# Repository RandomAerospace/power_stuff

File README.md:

if you want to add more stuff, use library loader and set path of downloaded footprints to SAMACSYS_LIB_PDB on my repo!
additionally, please set path preferences based on relative path of the folder that you have pulled the github repo into.
Go to UREX PDB  folder under POWER DISTRIBUTION for the pimped up weather balloon PDB

Power board presentation:https://drive.google.com/file/d/1bSlgJGe3XdCi3mun8Qso9A9fgnM_BNgd/view?usp=sharing

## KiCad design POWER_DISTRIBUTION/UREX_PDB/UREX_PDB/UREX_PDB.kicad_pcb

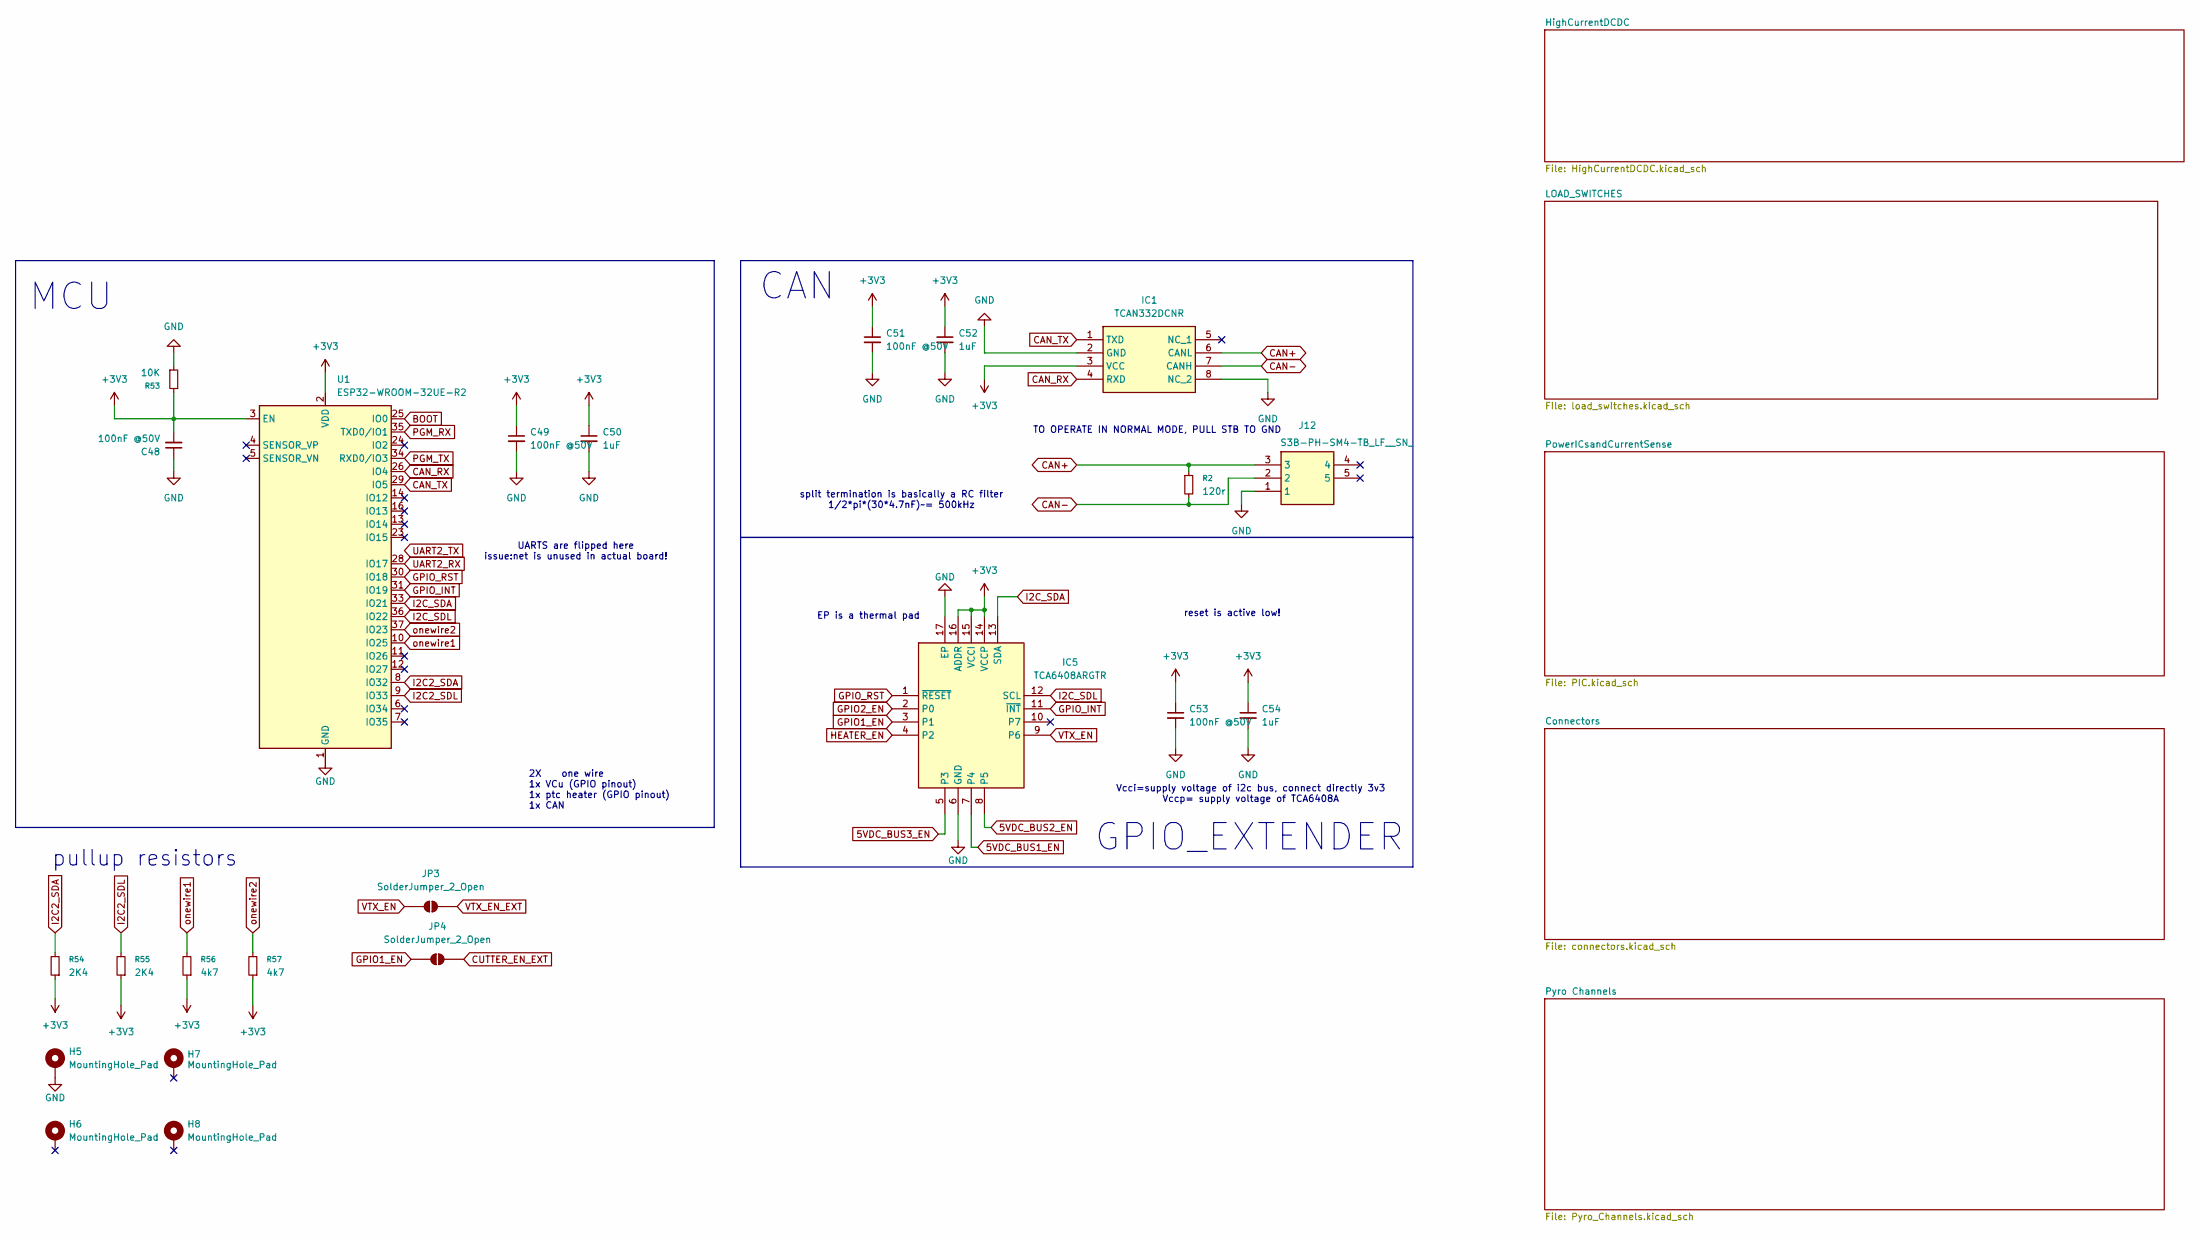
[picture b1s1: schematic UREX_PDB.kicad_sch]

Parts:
C48, C49, C51, C53: 100nF @50V; C_0603_1608Metric
C50, C52, C54: 1uF; C_0603_1608Metric
H5, H7, H8: MountingHole_Pad; MountingHole_2.2mm_M2_ISO7380
H6: MountingHole_Pad; MountingHole_2.2mm_M2_Pad_Via
IC1: TCAN332DCNR; SOT65P280X145-8N; Mouser Part Number 595-TCAN332DCNR
IC5: TCA6408ARGTR; QFN50P300X300X100-17N-D; Mouser Part Number 595-TCA6408ARGTR
J12: S3B-PH-SM4-TB_LF__SN_; S3BPHSM4TBLFSN; Mouser Part Number N/A
JP3, JP4: SolderJumper_2_Open; SolderJumper-2_P1.3mm_Open_Pad1.0x1.5mm
R2: 120r; R_0603_1608Metric
R53: 10K; R_0603_1608Metric
R54, R55: 2K4; R_0603_1608Metric
R56, R57: 4k7; R_0603_1608Metric
U1: ESP32-WROOM-32UE-R2; ESP32-WROOM-32UE

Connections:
5VDC_BUS1_EN: IC5.7 (P4); also elsewhere on the board
5VDC_BUS2_EN: IC5.8 (P5); also elsewhere on the board
5VDC_BUS3_EN: IC5.5 (P3); also elsewhere on the board
+3V3: C48.2, C49.1, C50.1, C51.1, C52.1, C53.1, C54.1, IC1.3 (VCC), IC5.14 (VCCP), IC5.15 (VCCI), IC5.16 (ADDR), R53.2, R54.1, R55.1, R56.1, R57.1, U1.2 (VDD), U1.3 (EN); also elsewhere on the board
BOOT: U1.25 (IO0); also elsewhere on the board
CAN+: IC1.6 (CANL), J12.3, R2.1
CAN-: IC1.7 (CANH), J12.2, R2.2
CAN_RX: IC1.4 (RXD), U1.26 (IO4)
CAN_TX: IC1.1 (TXD), U1.29 (IO5)
CUTTER_EN_EXT: JP4.2 (B); also elsewhere on the board
GND: C48.1, C49.2, C50.2, C51.2, C52.2, C53.2, C54.2, H5.1, IC1.2 (GND), IC1.8 (NC_2), IC5.6 (GND), IC5.17 (EP), J12.1, R53.1, U1.1 (GND), U1.15 (GND), U1.38 (GND), U1.39 (GND); also elsewhere on the board
GPIO1_EN: IC5.3 (P1), JP4.1 (A); also elsewhere on the board
GPIO2_EN: IC5.2 (P0); also elsewhere on the board
GPIO_INT: IC5.11 (~INT), U1.31 (IO19)
GPIO_RST: IC5.1 (~RESET), U1.30 (IO18)
HEATER_EN: IC5.4 (P2); also elsewhere on the board
I2C2_SDA: R54.2, U1.8 (IO32); also elsewhere on the board
I2C2_SDL: R55.2, U1.9 (IO33); also elsewhere on the board
I2C_SDA: IC5.13 (SDA), U1.33 (IO21)
I2C_SDL: IC5.12 (SCL), U1.36 (IO22)
PGM_RX: U1.35 (TXD0/IO1); also elsewhere on the board
PGM_TX: U1.34 (RXD0/IO3); also elsewhere on the board
UART2_RX: U1.28 (IO17)
VTX_EN: IC5.9 (P6), JP3.1 (A); also elsewhere on the board
VTX_EN_EXT: JP3.2 (B); also elsewhere on the board
onewire1: R56.2, U1.10 (IO25); also elsewhere on the board
onewire2: R57.2, U1.37 (IO23); also elsewhere on the board

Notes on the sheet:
UARTS are flipped here issue:net is unused in actual board!
TO OPERATE IN NORMAL MODE, PULL STB TO GND
reset is active low!
pullup resistors
Vcci=supply voltage of i2c bus, connect directly 3v3 Vccp= supply voltage of TCA6408A
MCU
EP is a thermal pad
2X one wire 1x VCu (GPIO pinout) 1x ptc heater (GPIO pinout) 1x CAN
GPIO_EXTENDER
split termination is basically a RC filter 1/2*pi*(30*4.7nF)~= 500kHz
CAN

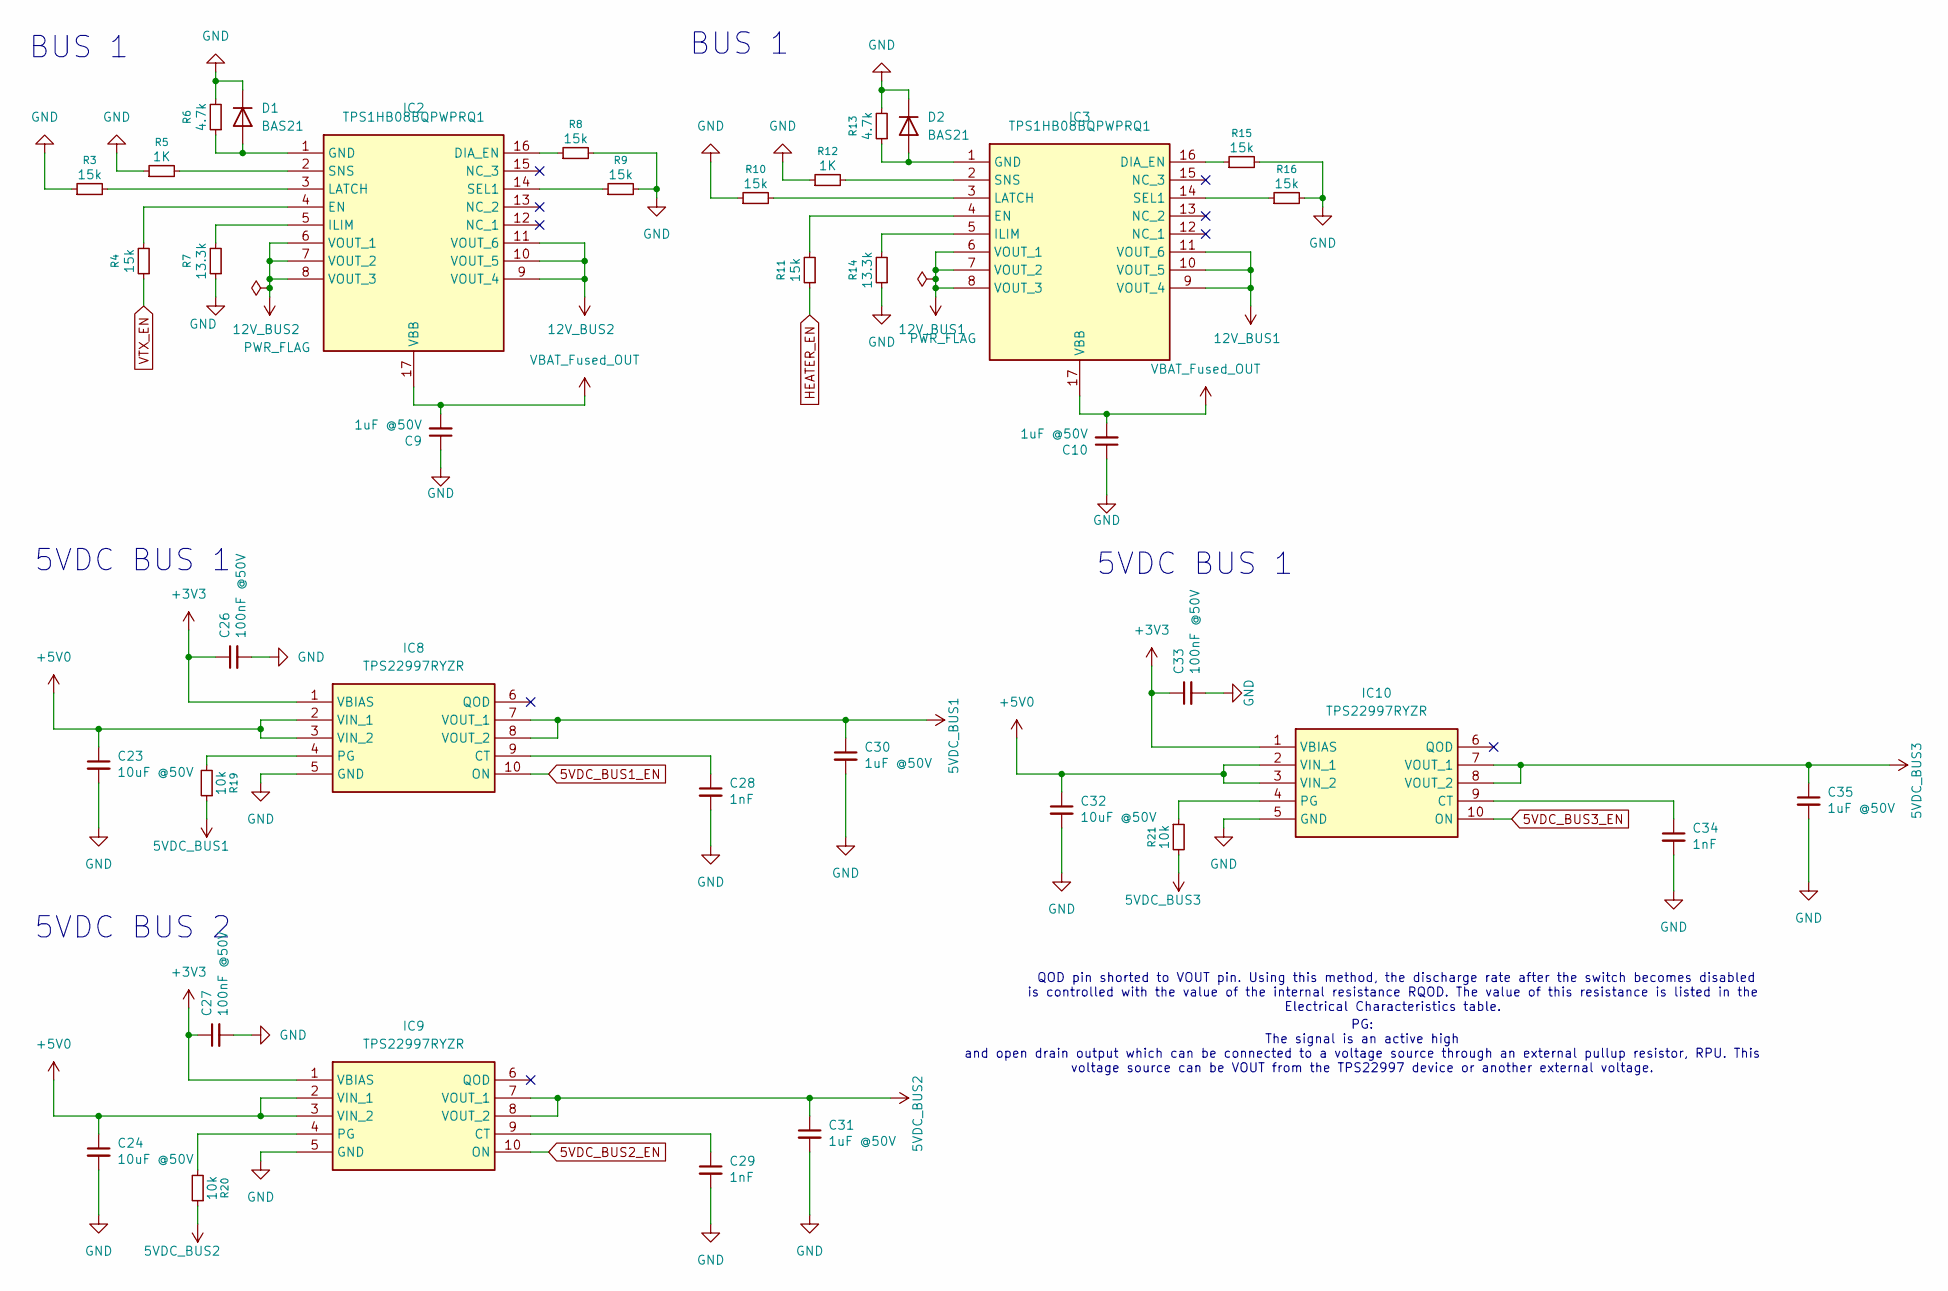
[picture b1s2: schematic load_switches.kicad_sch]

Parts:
C9, C10: 1uF @50V; C_0805_2012Metric_Pad1.18x1.45mm_HandSolder
C23, C24: 10uF @50V; C_1210_3225Metric_Pad1.33x2.70mm_HandSolder; Manufacturer_Part_Number GRM32EC72A106KE05L
C26, C27, C33: 100nF @50V; C_0402_1005Metric_Pad0.74x0.62mm_HandSolder
C28, C29, C34: 1nF; C_0603_1608Metric
C30, C31, C35: 1uF @50V; C_0805_2012Metric
C32: 10uF @50V; C_1210_3225Metric; Manufacturer_Part_Number GRM32EC72A106KE05L
D1, D2: BAS21; SOT-23
IC2, IC3: TPS1HB08BQPWPRQ1; SOP65P640X120-17N; Mouser Part Number 595-TPS1HB08BQPWPRQ1
IC8, IC9, IC10: TPS22997RYZR; Mouser Part Number 595-TPS22997RYZR
R3, R4, R8, R9, R10, R11, R15, R16: 15k; R_0603_1608Metric
R5, R12: 1K; R_0603_1608Metric
R6, R13: 4.7k; R_0603_1608Metric
R7, R14: 13.3k; R_0603_1608Metric
R19, R20, R21: 10k; R_0402_1005Metric_Pad0.72x0.64mm_HandSolder

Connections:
5VDC_BUS1: C30.1, IC8.7 (VOUT_1), IC8.8 (VOUT_2), R19.1; also elsewhere on the board
5VDC_BUS1_EN: IC8.10 (ON); also elsewhere on the board
5VDC_BUS2: C31.1, IC9.7 (VOUT_1), IC9.8 (VOUT_2), R20.1; also elsewhere on the board
5VDC_BUS2_EN: IC9.10 (ON); also elsewhere on the board
5VDC_BUS3: C35.1, IC10.7 (VOUT_1), IC10.8 (VOUT_2), R21.2; also elsewhere on the board
5VDC_BUS3_EN: IC10.10 (ON); also elsewhere on the board
12V_BUS1: IC3.6 (VOUT_1), IC3.7 (VOUT_2), IC3.8 (VOUT_3), IC3.9 (VOUT_4), IC3.10 (VOUT_5), IC3.11 (VOUT_6); also elsewhere on the board
12V_BUS2: IC2.6 (VOUT_1), IC2.7 (VOUT_2), IC2.8 (VOUT_3), IC2.9 (VOUT_4), IC2.10 (VOUT_5), IC2.11 (VOUT_6); also elsewhere on the board
+3V3: C26.1, C27.1, C33.1, IC8.1 (VBIAS), IC9.1 (VBIAS), IC10.1 (VBIAS); also elsewhere on the board
+5V0: C23.1, C24.1, C32.1, IC8.2 (VIN_1), IC8.3 (VIN_2), IC9.2 (VIN_1), IC9.3 (VIN_2), IC10.2 (VIN_1), IC10.3 (VIN_2); also elsewhere on the board
GND: C9.1, C10.1, C23.2, C24.2, C26.2, C27.2, C28.2, C29.2, C30.2, C31.2, C32.2, C33.2, C34.2, C35.2, D1.3 (K), D2.3 (K), IC8.5 (GND), IC9.5 (GND), IC10.5 (GND), R3.1, R5.1, R6.2, R7.1, R8.2, R9.2, R10.1, R12.1, R13.2, R14.1, R15.2, R16.2; also elsewhere on the board
HEATER_EN: R11.1; also elsewhere on the board
unnamed: D1.1 (A), IC2.1 (GND), R6.1
unnamed: D2.1 (A), IC3.1 (GND), R13.1
unnamed: IC2.16 (DIA_EN), R8.1
unnamed: IC2.4 (EN), R4.2
unnamed: IC2.5 (ILIM), R7.2
unnamed: IC2.3 (LATCH), R3.2
unnamed: IC2.14 (SEL1), R9.1
unnamed: IC2.2 (SNS), R5.2
unnamed: IC3.16 (DIA_EN), R15.1
unnamed: IC3.4 (EN), R11.2
unnamed: IC3.5 (ILIM), R14.2
unnamed: IC3.3 (LATCH), R10.2
unnamed: IC3.14 (SEL1), R16.1
unnamed: IC3.2 (SNS), R12.2
unnamed: C28.1, IC8.9 (CT)
unnamed: IC8.4 (PG), R19.2
unnamed: C29.1, IC9.9 (CT)
unnamed: IC9.4 (PG), R20.2
unnamed: C34.1, IC10.9 (CT)
unnamed: IC10.4 (PG), R21.1
VBAT_Fused_OUT: C9.2, C10.2, IC2.17 (VBB), IC3.17 (VBB); also elsewhere on the board
VTX_EN: R4.1; also elsewhere on the board

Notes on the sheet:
5VDC BUS 2
BUS 1
5VDC BUS 1
PG: The signal is an active high and open drain output which can be connected to a voltage source through an external pullup resistor, RPU. This voltage source can be VOUT from the TPS22997 device or another external voltage.
QOD pin shorted to VOUT pin. Using this method, the discharge rate after the switch becomes disabled is controlled with the value of the internal resistance RQOD. The value of this resistance is listed in the Electrical Characteristics table.

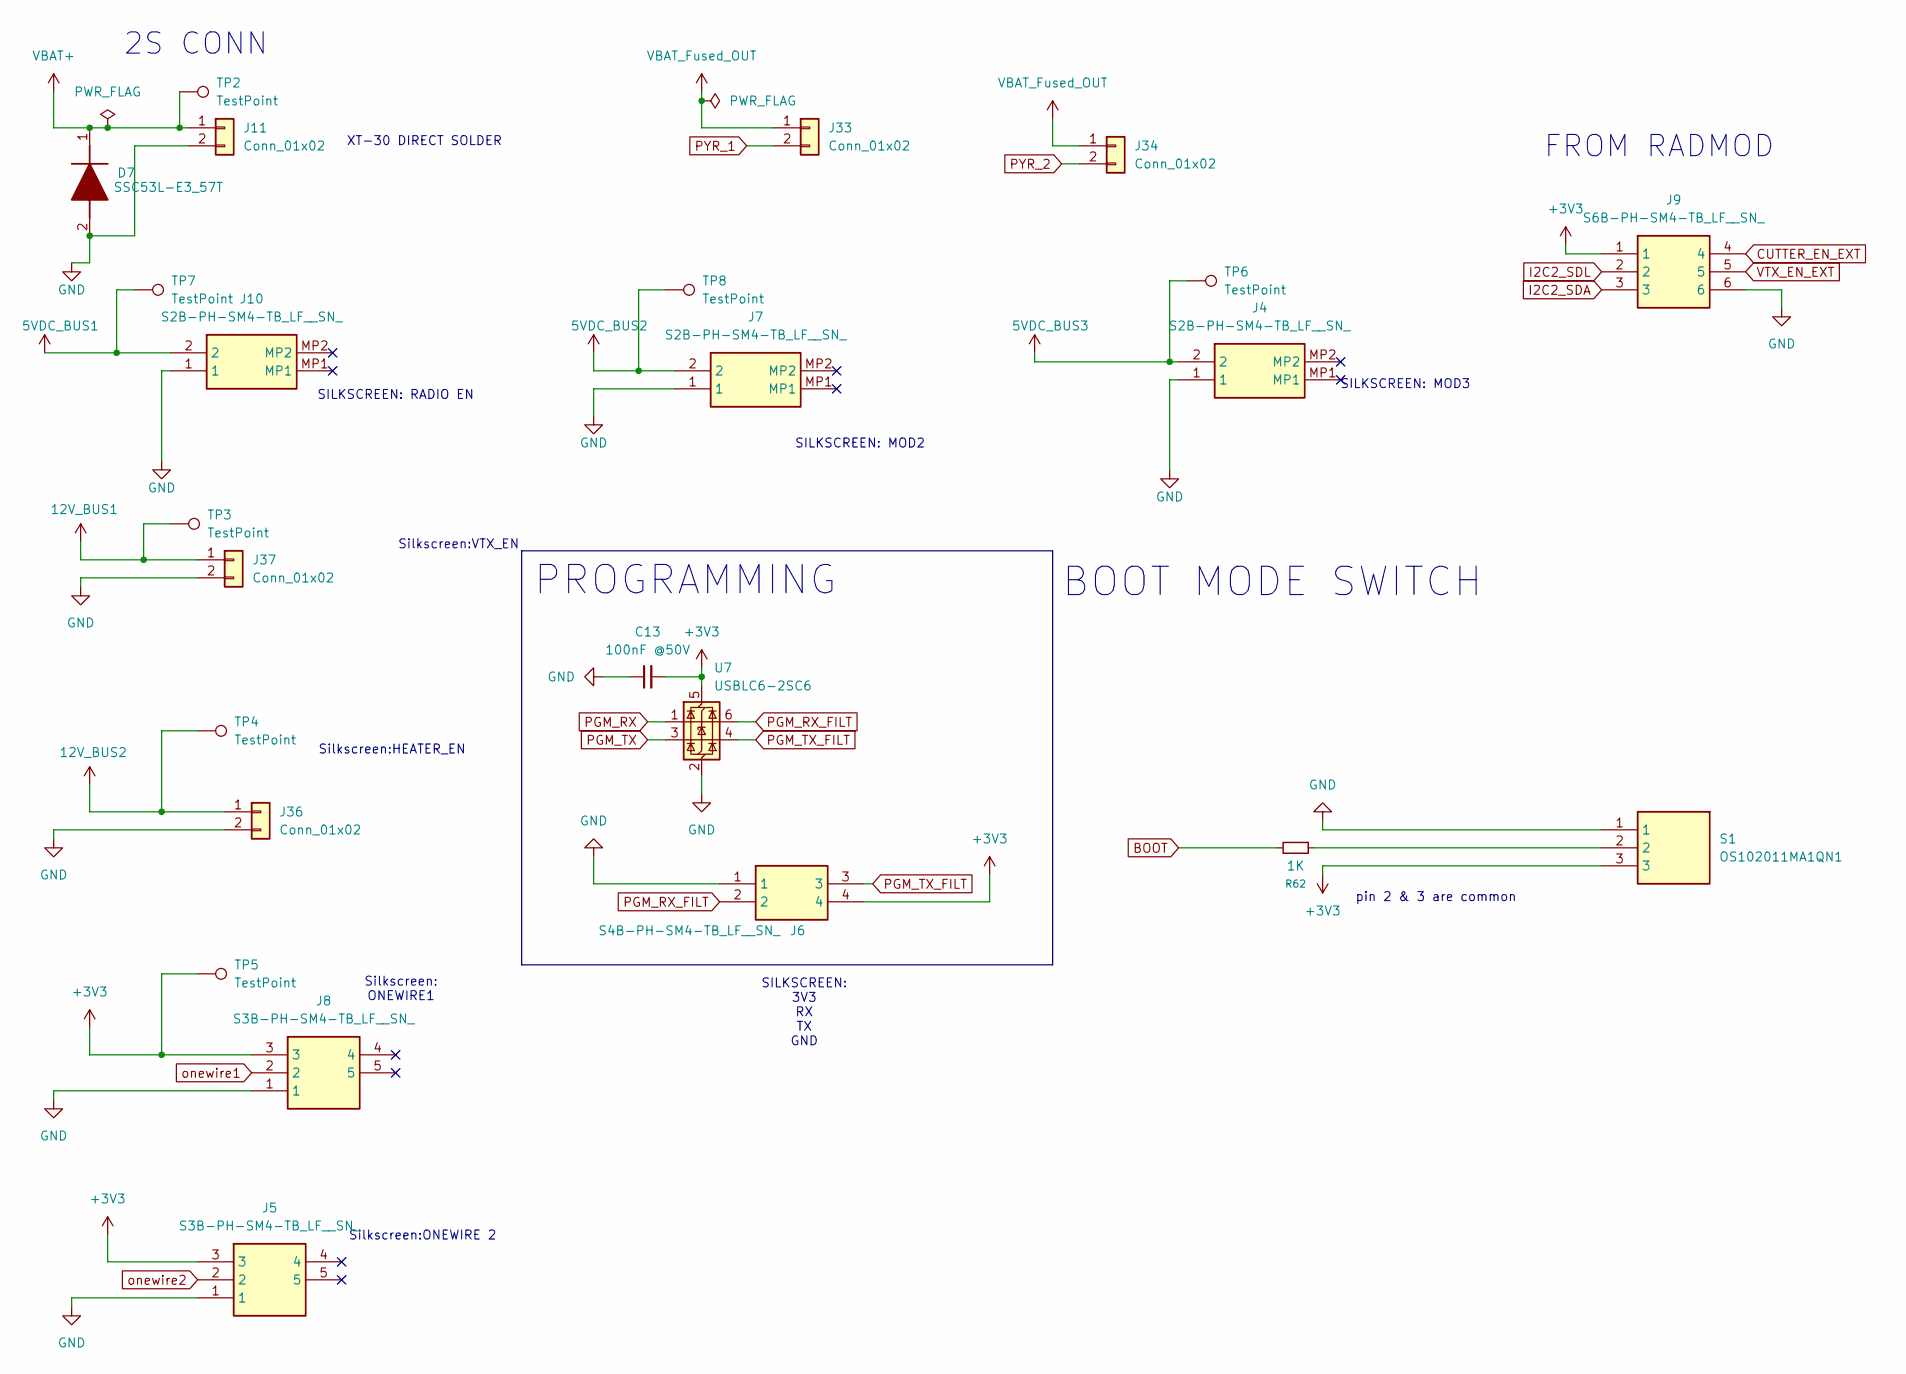
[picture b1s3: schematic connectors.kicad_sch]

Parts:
C13: 100nF @50V; C_0603_1608Metric
D7: SSC53L-E3_57T; DIOM7959X262N; Manufacturer_Part_Number SSC53L-E3/57T; Mouser Part Number 625-SSC53L-E3
J4, J7, J10: S2B-PH-SM4-TB_LF__SN_; S2BPHSM4TBLFSN; Mouser Part Number N/A
J5, J8: S3B-PH-SM4-TB_LF__SN_; S3BPHSM4TBLFSN; Mouser Part Number N/A
J6: S4B-PH-SM4-TB_LF__SN_; S4B-PH-SM4-TB; Mouser Part Number N/A
J9: S6B-PH-SM4-TB_LF__SN_; S6B-PH-SM4-TB_LF__SN__3; Mouser Part Number N/A
J11: Conn_01x02; AMASS_XT30U-F_1x02_P5.0mm_Vertical
J33, J34, J36, J37: Conn_01x02; JST_PH_S2B-PH-K_1x02_P2.00mm_Horizontal
R62: 1K; R_0603_1608Metric
S1: OS102011MA1QN1; SW_Slide_SPDT_Angled_CK_OS102011MA1Q; Manufacturer_Part_Number OS102011MA1QN1; Mouser Part Number 611-OS102011MA1QN1
TP2, TP3, TP4, TP5, TP6, TP7, TP8: TestPoint; TestPoint_Pad_D1.0mm
U7: USBLC6-2SC6; SOT-23-6

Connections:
5VDC_BUS1: J10.2, TP7.1 (1_1); also elsewhere on the board
5VDC_BUS2: J7.2, TP8.1 (1_1); also elsewhere on the board
5VDC_BUS3: J4.2, TP6.1 (1_1); also elsewhere on the board
12V_BUS1: J37.1, TP3.1 (1_1); also elsewhere on the board
12V_BUS2: J36.1, TP4.1 (1_1); also elsewhere on the board
+3V3: C13.2, J5.3, J6.4, J8.3, J9.1, S1.3, TP5.1 (1_1), U7.5 (VBUS); also elsewhere on the board
BOOT: R62.2; also elsewhere on the board
CUTTER_EN_EXT: J9.4; also elsewhere on the board
GND: C13.1, D7.2 (A), J4.1, J5.1, J6.1, J7.1, J8.1, J9.6, J10.1, J11.2, J36.2, J37.2, S1.1, U7.2 (GND); also elsewhere on the board
I2C2_SDA: J9.3; also elsewhere on the board
I2C2_SDL: J9.2; also elsewhere on the board
unnamed: R62.1, S1.2
PGM_RX: U7.1 (I/O1); also elsewhere on the board
PGM_RX_FILT: J6.2, U7.6 (I/O1)
PGM_TX: U7.3 (I/O2); also elsewhere on the board
PGM_TX_FILT: J6.3, U7.4 (I/O2)
PYR_1: J33.2; also elsewhere on the board
PYR_2: J34.2; also elsewhere on the board
VBAT+: D7.1 (K), J11.1, TP2.1 (1_1); also elsewhere on the board
VBAT_Fused_OUT: J33.1, J34.1; also elsewhere on the board
VTX_EN_EXT: J9.5; also elsewhere on the board
onewire1: J8.2; also elsewhere on the board
onewire2: J5.2; also elsewhere on the board

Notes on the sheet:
pin 2 & 3 are common
SILKSCREEN: 3V3 RX TX GND
2S CONN
BOOT MODE SWITCH
Silkscreen: ONEWIRE1
Silkscreen:ONEWIRE 2
XT-30 DIRECT SOLDER
Silkscreen:HEATER_EN
SILKSCREEN: MOD2
SILKSCREEN: MOD3
SILKSCREEN: RADIO EN
Silkscreen:VTX_EN
PROGRAMMING
FROM RADMOD

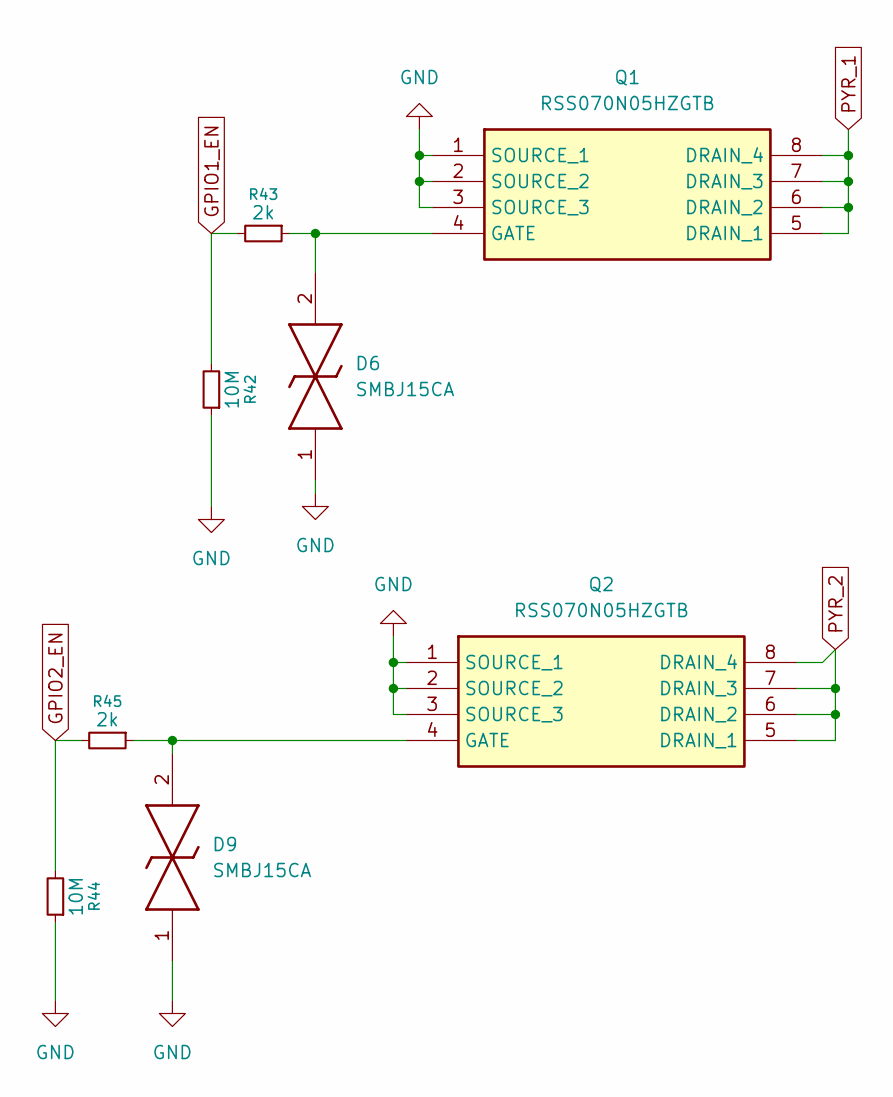
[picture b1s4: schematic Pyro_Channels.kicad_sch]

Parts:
D6, D9: SMBJ15CA; DIONM5436X244N; Mouser Part Number 947-SMBJ15CA
Q1, Q2: RSS070N05HZGTB; SOIC127P600X175-8N; Manufacturer_Part_Number RSS070N05HZGTB; Mouser Part Number 755-RSS070N05HZGTB
R42, R44: 10M; R_0603_1608Metric
R43, R45: 2k; R_0603_1608Metric

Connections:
GND: D6.1, D9.1, Q1.1 (SOURCE_1), Q1.2 (SOURCE_2), Q1.3 (SOURCE_3), Q2.1 (SOURCE_1), Q2.2 (SOURCE_2), Q2.3 (SOURCE_3), R42.1, R44.1; also elsewhere on the board
GPIO1_EN: R42.2, R43.2; also elsewhere on the board
GPIO2_EN: R44.2, R45.2; also elsewhere on the board
unnamed: D6.2, Q1.4 (GATE), R43.1
unnamed: D9.2, Q2.4 (GATE), R45.1
PYR_1: Q1.5 (DRAIN_1), Q1.6 (DRAIN_2), Q1.7 (DRAIN_3), Q1.8 (DRAIN_4); also elsewhere on the board
PYR_2: Q2.5 (DRAIN_1), Q2.6 (DRAIN_2), Q2.7 (DRAIN_3), Q2.8 (DRAIN_4); also elsewhere on the board

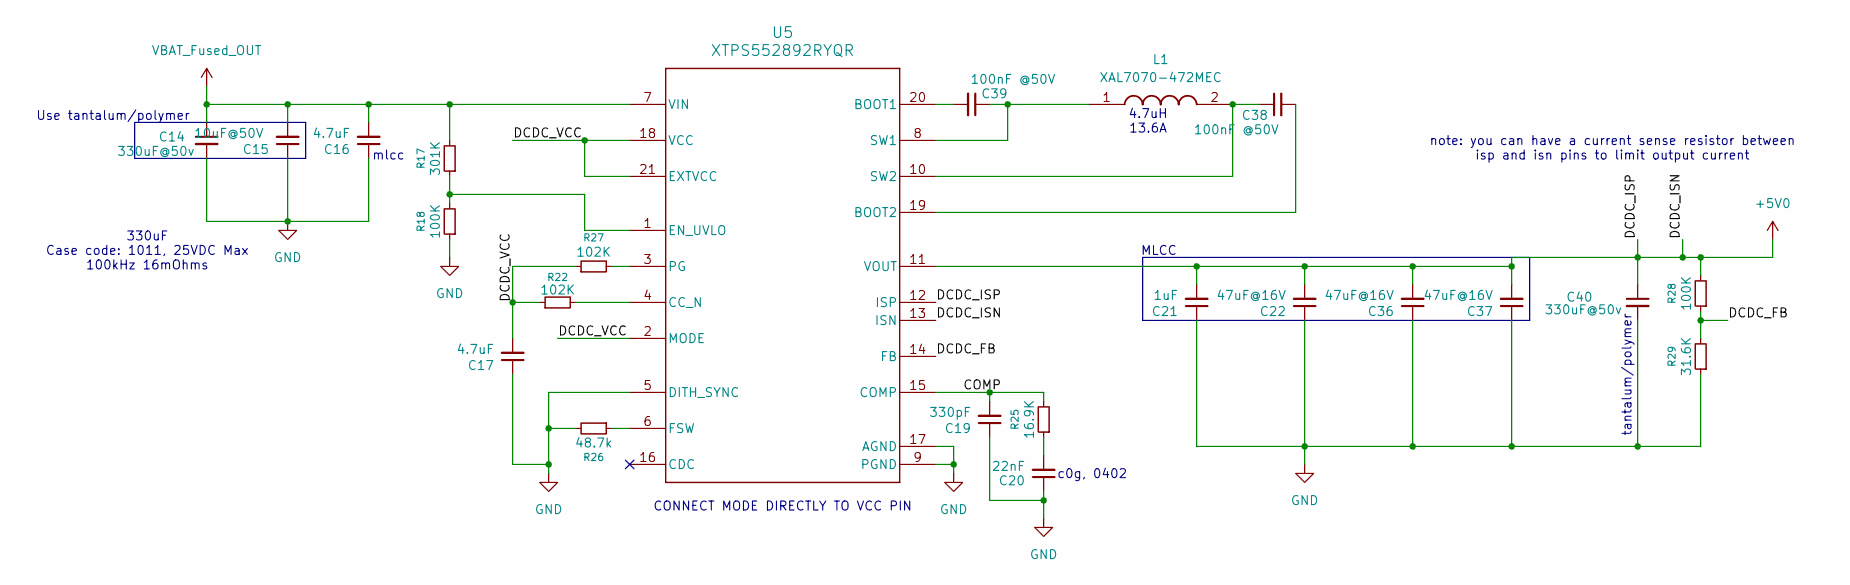
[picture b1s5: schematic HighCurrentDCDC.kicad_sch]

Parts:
C14, C40: 330uF@50v; CP_Radial_D10.0mm_P5.00mm; Manufacturer_Part_Number RHA1011331M025K
C15: 10uF@50V; C_1210_3225Metric; Manufacturer_Part_Number GRM32EC72A106KE05L
C16, C17: 4.7uF; C_0805_2012Metric_Pad1.18x1.45mm_HandSolder
C19: 330pF; C_0603_1608Metric
C20: 22nF; C_0603_1608Metric
C21: 1uF; C_0805_2012Metric_Pad1.18x1.45mm_HandSolder
C22, C36, C37: 47uF@16V; C_1210_3225Metric; Manufacturer_Part_Number GRM31CR61C476ME44L
C38, C39: 100nF @50V; C_0402_1005Metric_Pad0.74x0.62mm_HandSolder
L1: XAL7070-472MEC; XAL7070472MEC; Mouser Part Number 994-XAL7070-472MEC
R17: 301K; R_0603_1608Metric
R18, R28: 100K; R_0603_1608Metric
R22, R27: 102K; R_0603_1608Metric
R25: 16.9K; R_0603_1608Metric
R26: 48.7k; R_0603_1608Metric
R29: 31.6K; R_0603_1608Metric
U5: XTPS552892RYQR; RYQ0021A-MFG

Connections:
+5V0: C21.2, C22.2, C36.2, C37.2, C40.1, R28.2, U5.11 (VOUT), U5.12 (ISP), U5.13 (ISN); also elsewhere on the board
/HighCurrentDCDC/COMP: C19.2, R25.2, U5.15 (COMP)
/HighCurrentDCDC/DCDC_FB: R28.1, R29.2, U5.14 (FB)
/HighCurrentDCDC/DCDC_VCC: C17.2, R22.1, R27.1, U5.2 (MODE), U5.18 (VCC), U5.21 (EXTVCC)
GND: C14.2, C15.1, C16.1, C17.1, C19.1, C20.1, C21.1, C22.1, C36.1, C37.1, C40.2, R18.1, R26.2, R29.1, U5.5 (DITH_SYNC), U5.9 (PGND), U5.17 (AGND); also elsewhere on the board
unnamed: C20.2, R25.1
unnamed: C39.2, U5.20 (BOOT1)
unnamed: C38.2, U5.19 (BOOT2)
unnamed: R22.2, U5.4 (CC_N)
unnamed: R17.1, R18.2, U5.1 (EN_UVLO)
unnamed: R26.1, U5.6 (FSW)
unnamed: R27.2, U5.3 (PG)
unnamed: C39.1, L1.1, U5.8 (SW1)
unnamed: C38.1, L1.2, U5.10 (SW2)
VBAT_Fused_OUT: C14.1, C15.2, C16.2, R17.2, U5.7 (VIN); also elsewhere on the board

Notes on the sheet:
4.7uH 13.6A
tantalum/polymer
c0g, 0402
CONNECT MODE DIRECTLY TO VCC PIN
note: you can have a current sense resistor between isp and isn pins to limit output current
330uF Case code: 1011, 25VDC Max 100kHz 16mOhms
MLCC
Use tantalum/polymer
mlcc

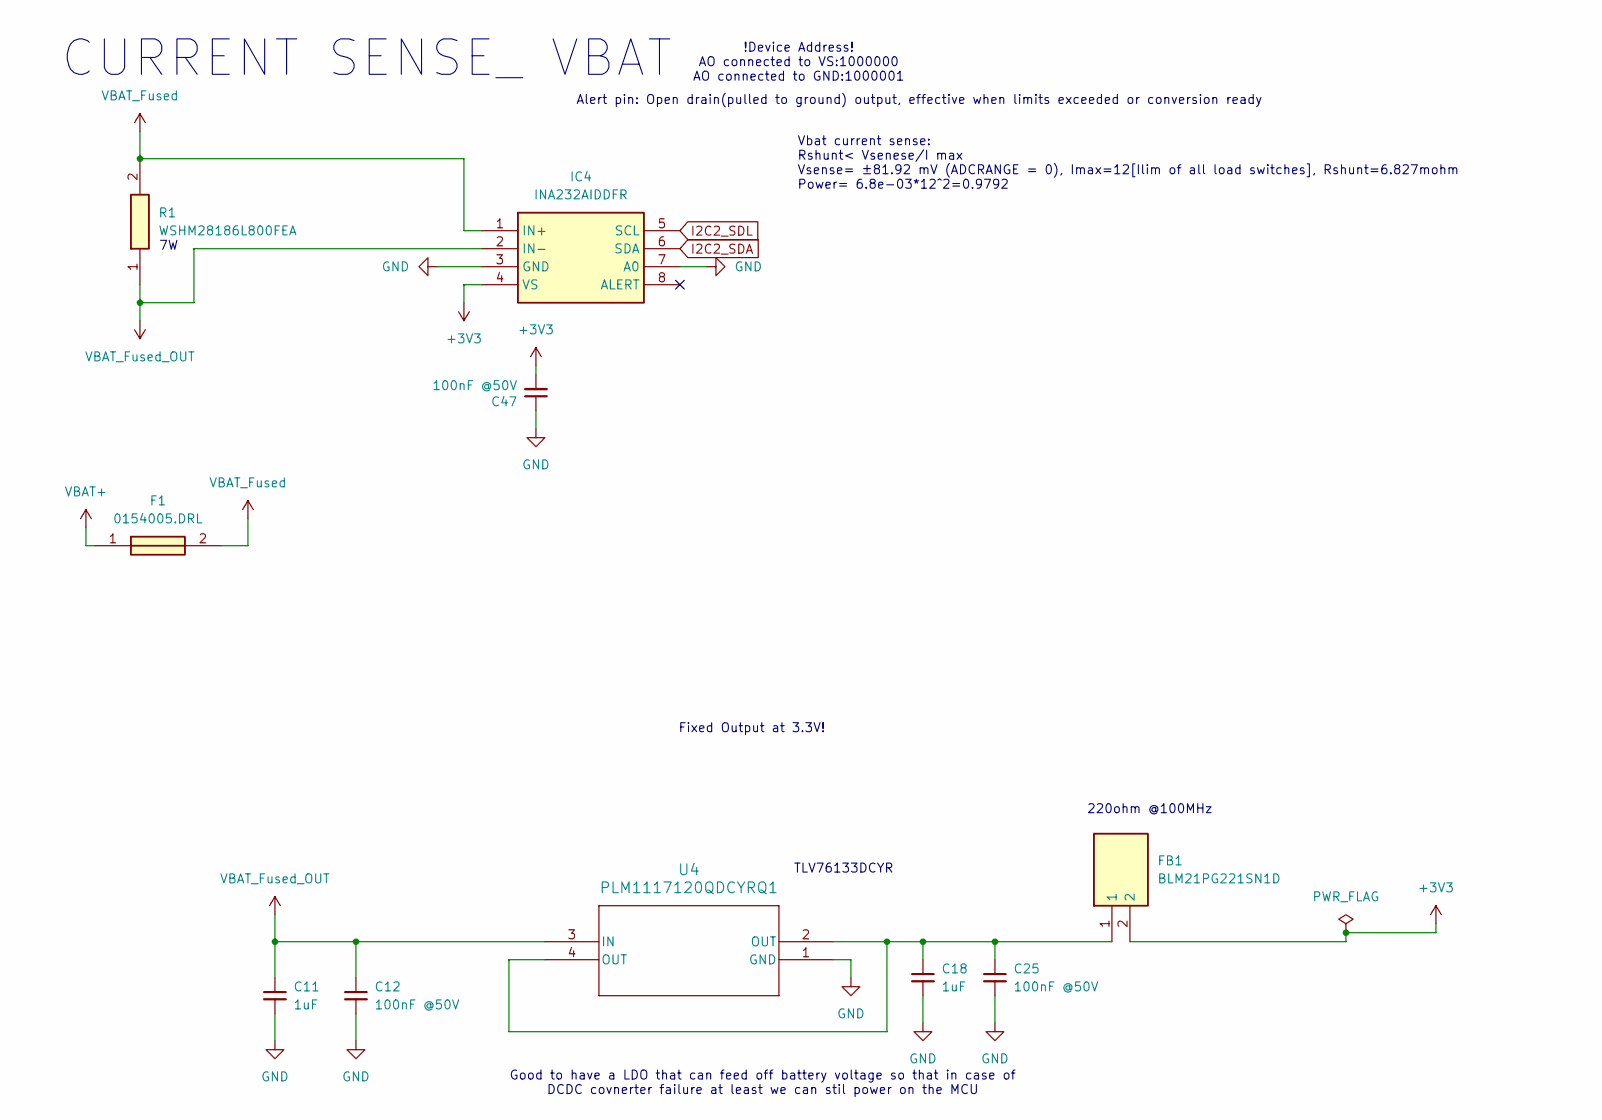
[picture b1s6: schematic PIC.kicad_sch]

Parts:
C11, C18: 1uF; C_0603_1608Metric
C12, C25: 100nF @50V; C_0603_1608Metric
C47: 100nF @50V; C_0402_1005Metric_Pad0.74x0.62mm_HandSolder
F1: 0154005.DRL; 0154005DRL; Manufacturer_Part_Number 0154005.DRL; Mouser Part Number 576-0154005.DRL
FB1: BLM21PG221SN1D; BEADC2012X105N; Manufacturer_Part_Number BLM21PG221SN1D; Mouser Part Number 81-BLM21P221SG
IC4: INA232AIDDFR; SOT65P280X110-8N; Manufacturer_Part_Number INA232AIDDFR; Mouser Part Number 595-INA232AIDDFR
R1: WSHM28186L800FEA; WSHM2818R0330FEB; Manufacturer_Part_Number WSHM28186L800FEA; Mouser Part Number 71-WSHM28186L800FEA
U4: PLM1117120QDCYRQ1; SOT-223-4_DCY_TEX

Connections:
+3V3: C47.2, FB1.2, IC4.4 (VS); also elsewhere on the board
GND: C11.2, C12.2, C18.2, C25.2, C47.1, IC4.3 (GND), IC4.7 (A0), U4.1 (GND); also elsewhere on the board
I2C2_SDA: IC4.6 (SDA); also elsewhere on the board
I2C2_SDL: IC4.5 (SCL); also elsewhere on the board
unnamed: C18.1, C25.1, FB1.1, U4.2 (OUT), U4.4 (OUT)
VBAT+: F1.1; also elsewhere on the board
VBAT_Fused: F1.2, IC4.1 (IN+), R1.2
VBAT_Fused_OUT: C11.1, C12.1, IC4.2 (IN-), R1.1, U4.3 (IN); also elsewhere on the board

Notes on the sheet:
CURRENT SENSE_ VBAT
TLV76133DCYR
!Device Address! AO connected to VS:1000000 AO connected to GND:1000001
Vbat current sense: Rshunt< Vsenese/I max Vsense= ±81.92 mV (ADCRANGE = 0), Imax=12[Ilim of all load switches], Rshunt=6.827mohm Power= 6.8e-03*12^2=0.9792
220ohm @100MHz
Alert pin: Open drain(pulled to ground) output, effective when limits exceeded or conversion ready
Fixed Output at 3.3V!
Good to have a LDO that can feed off battery voltage so that in case of DCDC covnerter failure at least we can stil power on the MCU

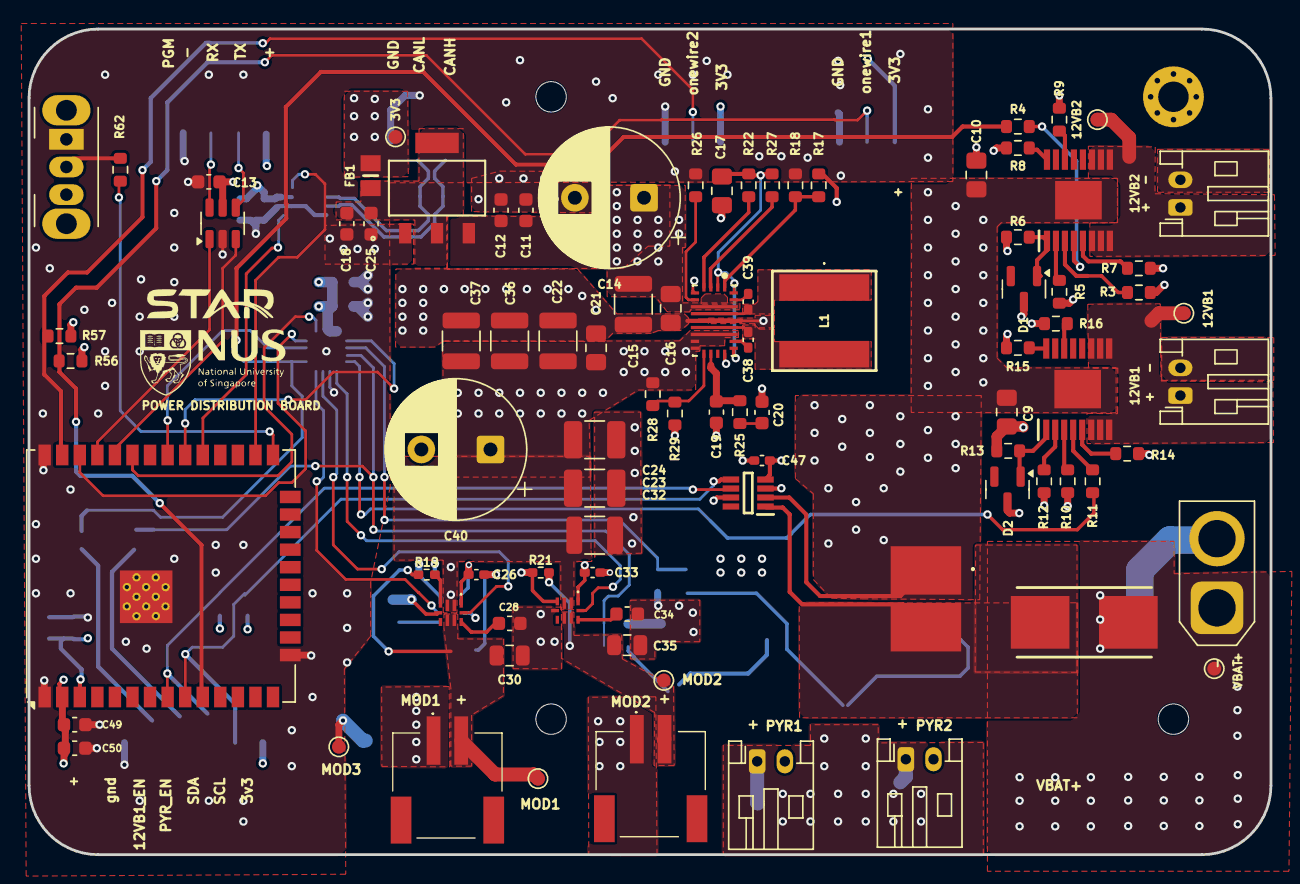
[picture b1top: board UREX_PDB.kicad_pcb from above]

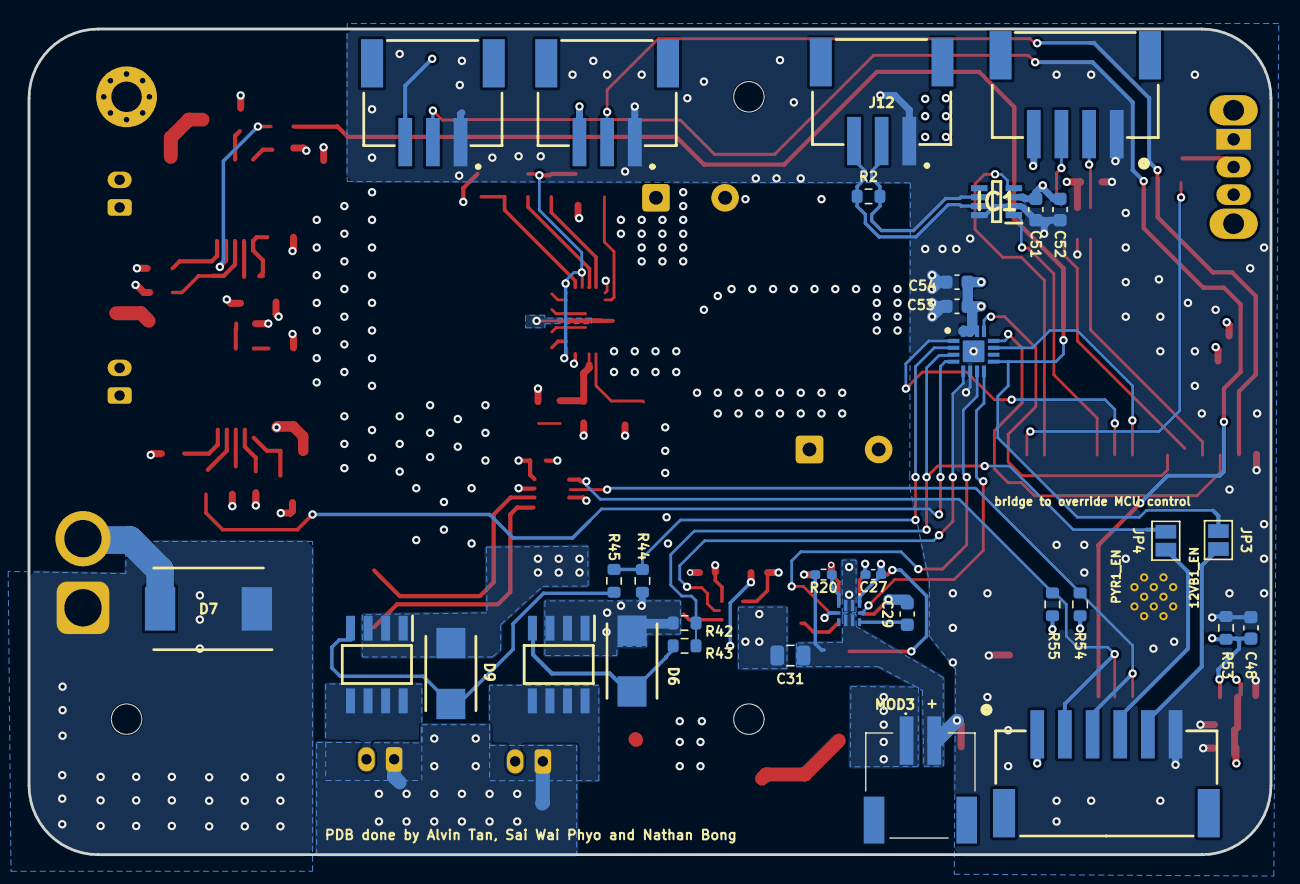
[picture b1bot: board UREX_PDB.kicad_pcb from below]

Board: 4 copper layers, 89.8 x 59.7 mm, 126 parts (33 on the bottom side), 75 nets.

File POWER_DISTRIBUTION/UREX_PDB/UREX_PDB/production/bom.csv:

Designator,Footprint,Quantity,Value,LCSC Part #
"C10, C30, C31, C35, C9",0805,5,1uF @50V,
"C11, C18, C50, C52, C54",0603,5,1uF,
"C12, C13, C25, C48, C49, C51, C53",0603,7,100nF @50V,
"C14, C40",CP_Radial_D10.0mm_P5.00mm,2,330uF@50v,
C15,1210,1,10uF@50V,
"C16, C17",0805,2,4.7uF,
C19,0603,1,330pF,
C20,0603,1,22nF,
C21,0805,1,1uF,
"C22, C36, C37",1210,3,47uF@16V,
"C23, C24, C32",1210,3,10uF @50V,
"C26, C27, C33, C38, C39, C47",0402,6,100nF @50V,
"C28, C29, C34",0603,3,1nF,
"D1, D2",SOT-23,2,BAS21,
"D6, D9",DIONM5436X244N,2,SMBJ15CA,
D7,DIOM7959X262N,1,SSC53L-E3_57T,
F1,0154005DRL,1,0154005.DRL,
FB1,BEADC2012X105N,1,BLM21PG221SN1D,
"H5, H7, H8",MountingHole_2.2mm_M2_ISO7380,3,MountingHole_Pad,
H6,MountingHole_2.2mm_M2_Pad_Via,1,MountingHole_Pad,
IC1,SOT65P280X110-8N,1,TCAN1044VDDFR,
"IC10, IC8, IC9",TPS22997RYZR,3,TPS22997RYZR,
"IC2, IC3",SOP65P640X120-17N,2,TPS1HB08BQPWPRQ1,
IC4,SOT65P280X110-8N,1,INA232AIDDFR,
IC5,QFN50P300X300X100-17N-D,1,TCA6408ARGTR,
"J10, J4, J7",S2BPHSM4TBLFSN,3,S2B-PH-SM4-TB_LF__SN_,
J11,AMASS_XT30U-F_1x02_P5.0mm_Vertical,1,Conn_01x02,
"J12, J5, J8",S3BPHSM4TBLFSN,3,S3B-PH-SM4-TB_LF__SN_,
"J33, J34, J36, J37",JST_PH_S2B-PH-K_1x02_P2.00mm_Horizontal,4,Conn_01x02,
J6,S4B-PH-SM4-TB,1,S4B-PH-SM4-TB_LF__SN_,
J9,S6B-PH-SM4-TB_LF__SN__3,1,S6B-PH-SM4-TB_LF__SN_,
L1,XAL7070472MEC,1,XAL7070-472MEC,
"Q1, Q2",SOIC127P600X175-8N,2,RSS070N05HZGTB,
R1,WSHM2818R0330FEB,1,WSHM28186L800FEA,
"R10, R11, R15, R16, R3, R4, R8, R9",0603,8,15k,
"R12, R5, R62",0603,3,1K,
"R13, R6",0603,2,4.7k,
"R14, R7",0603,2,13.3k,
R17,0603,1,301K,
"R18, R28",0603,2,100K,
"R19, R20, R21",0402,3,10k,
R2,0603,1,120r,
"R22, R27",0603,2,102K,
R25,0603,1,16.9K,
R26,0603,1,48.7k,
R29,0603,1,31.6K,
"R42, R44",0603,2,10M,
"R43, R45",0603,2,2k,
R53,0603,1,10K,
"R54, R55",0603,2,2K4,
"R56, R57",0603,2,4k7,
S1,SW_Slide_SPDT_Angled_CK_OS102011MA1Q,1,OS102011MA1QN1,
"TP2, TP3, TP4, TP5, TP6, TP7, TP8",TestPoint_Pad_D1.0mm,7,TestPoint,
U1,ESP32-WROOM-32UE,1,ESP32-WROOM-32UE-R2,
U4,SOT-223-4_DCY_TEX,1,PLM1117120QDCYRQ1,
U5,RYQ0021A-MFG,1,XTPS552892RYQR,
U7,SOT-23-6,1,USBLC6-2SC6,
